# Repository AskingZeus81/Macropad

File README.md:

# Macropad
This is a project sparked by the great team of Hackpad. It's a simple macropad made with care. It includes 6 keys and 1 knob.

# Bill of Materials

Seeed XIAO RP2040 microcontroller,
6 pieces of MX-style mechanical switches,
6 pieces of Blank DSA keycaps,
EC11 rotary encoder (20mm D-shaft),
4 M3×16mm screws,
4 M3×5×4mm heatset inserts,

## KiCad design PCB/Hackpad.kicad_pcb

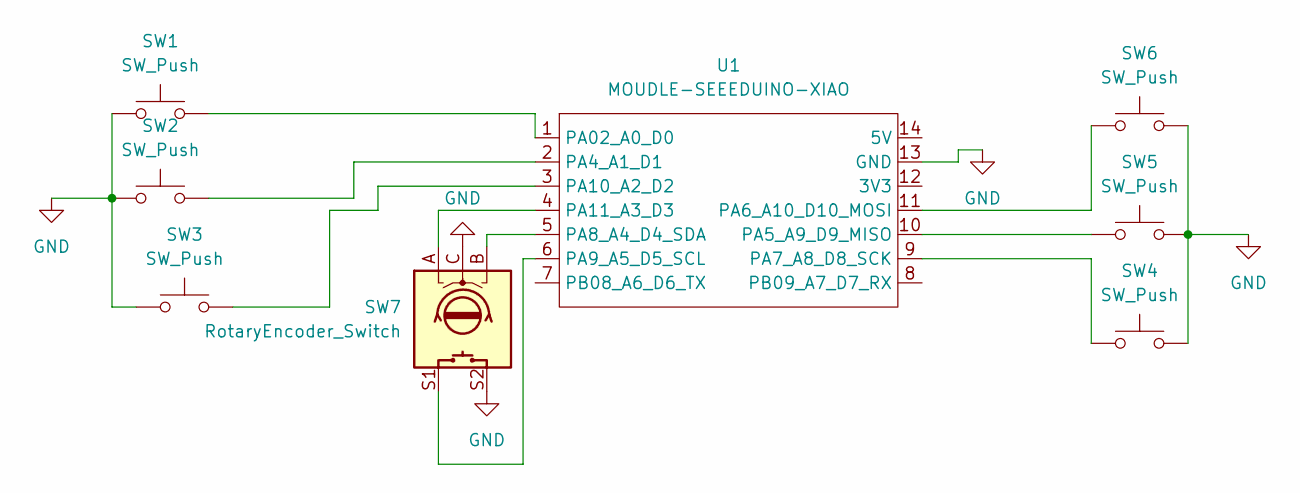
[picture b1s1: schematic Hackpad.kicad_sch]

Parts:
SW1, SW2, SW3, SW4, SW5, SW6: SW_Push; SW_Cherry_MX_1.00u_PCB
SW7: RotaryEncoder_Switch; RotaryEncoder_Alps_EC11E-Switch_Vertical_H20mm
U1: MOUDLE-SEEEDUINO-XIAO; XIAO-Generic-Hybrid-14P-2.54-21X17.8MM

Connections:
GND: SW1.1, SW2.1, SW3.1, SW4.1, SW5.1, SW6.1, SW7.C, SW7.S2, U1.13 (GND)
unnamed: SW1.2, U1.1 (PA02_A0_D0)
unnamed: SW2.2, U1.2 (PA4_A1_D1)
unnamed: SW5.2, U1.10 (PA5_A9_D9_MISO)
unnamed: SW6.2, U1.11 (PA6_A10_D10_MOSI)
unnamed: SW4.2, U1.9 (PA7_A8_D8_SCK)
unnamed: SW7.B, U1.5 (PA8_A4_D4_SDA)
unnamed: SW7.S1, U1.6 (PA9_A5_D5_SCL)
unnamed: SW3.2, U1.3 (PA10_A2_D2)
unnamed: SW7.A, U1.4 (PA11_A3_D3)

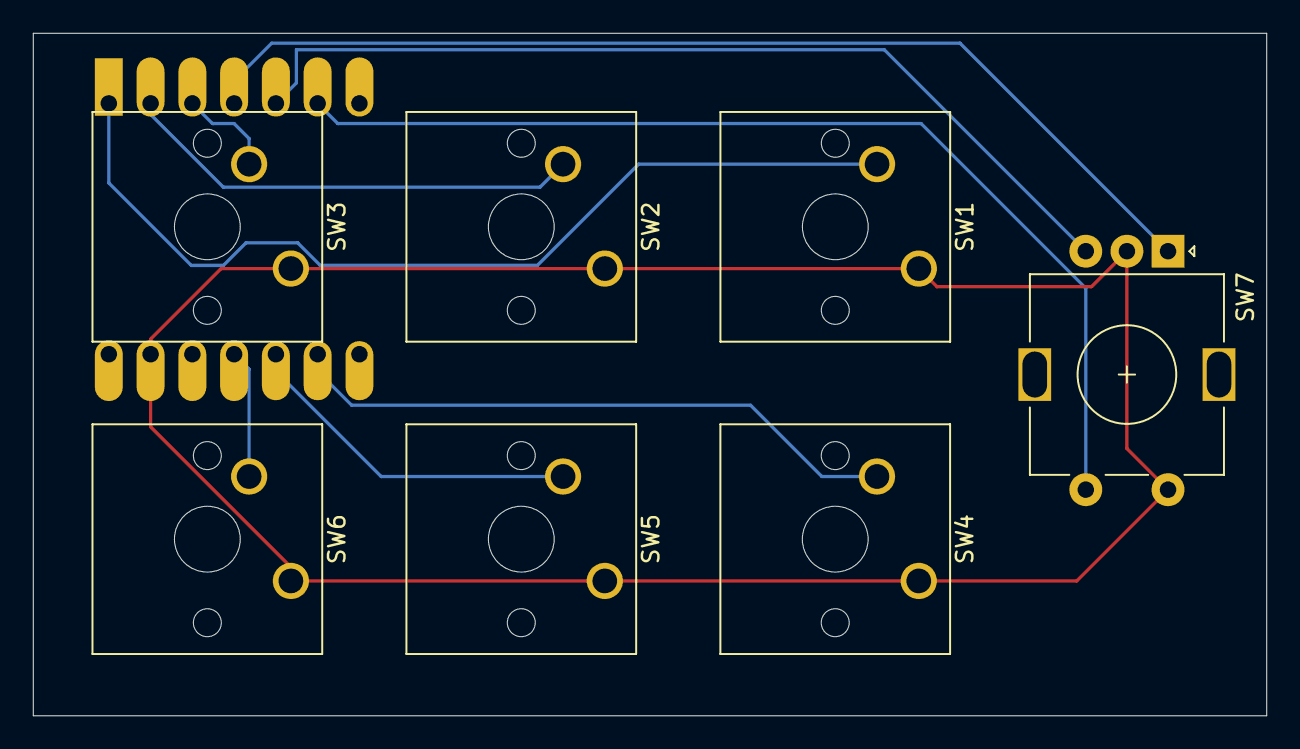
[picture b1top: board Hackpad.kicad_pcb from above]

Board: 2 copper layers, 75.0 x 41.5 mm, 8 parts (1 on the bottom side), 10 nets.

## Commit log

2026-06-13 README.md
